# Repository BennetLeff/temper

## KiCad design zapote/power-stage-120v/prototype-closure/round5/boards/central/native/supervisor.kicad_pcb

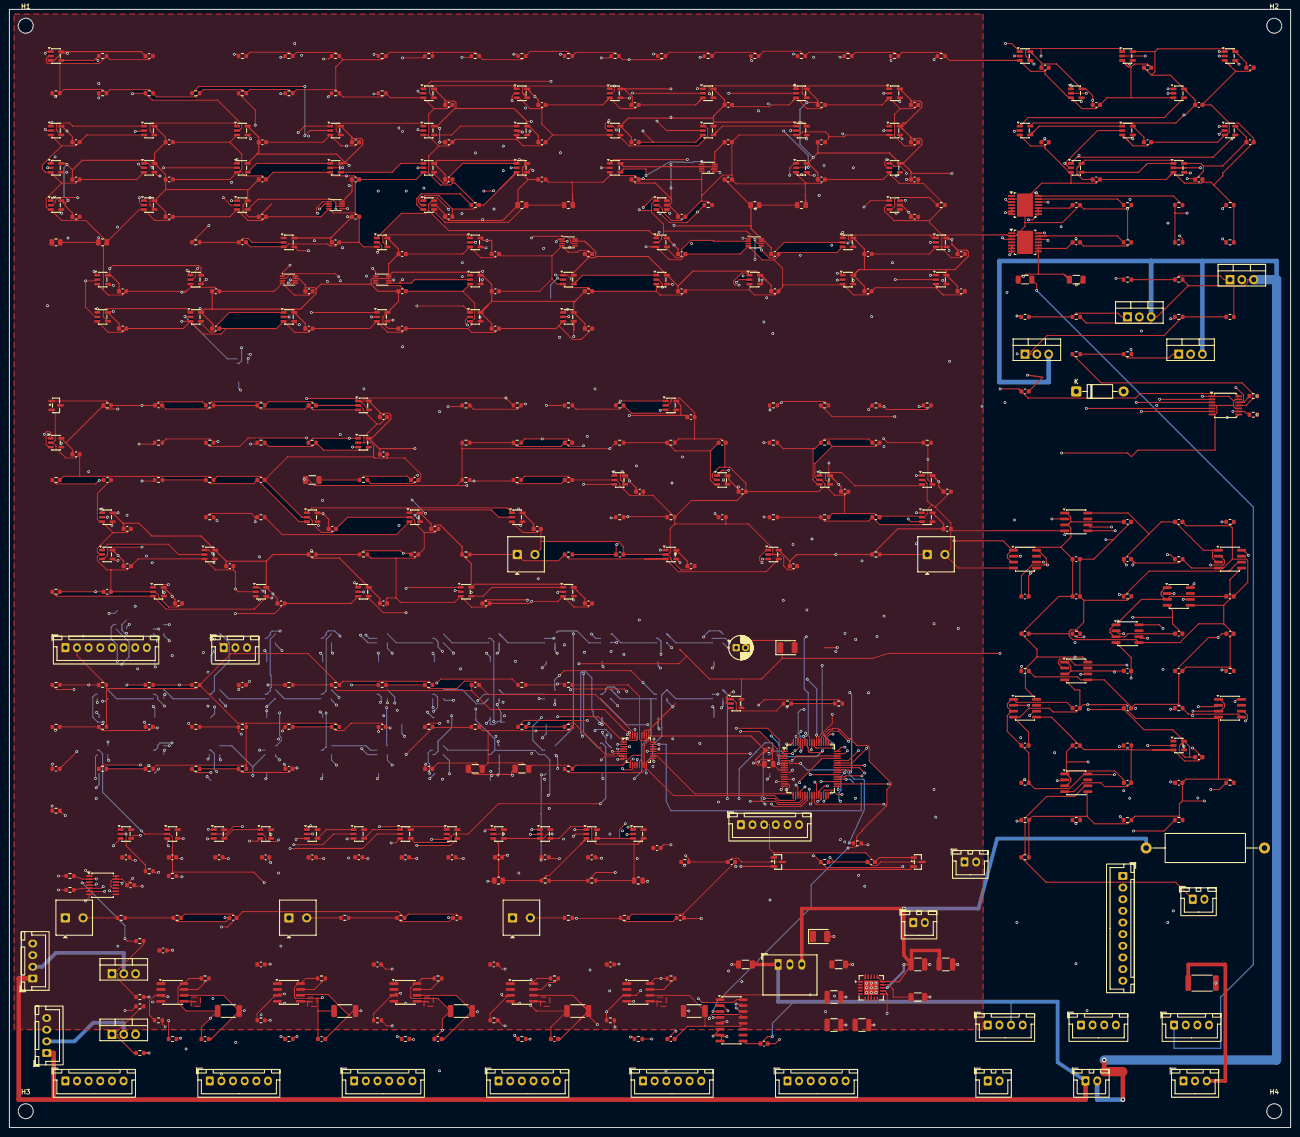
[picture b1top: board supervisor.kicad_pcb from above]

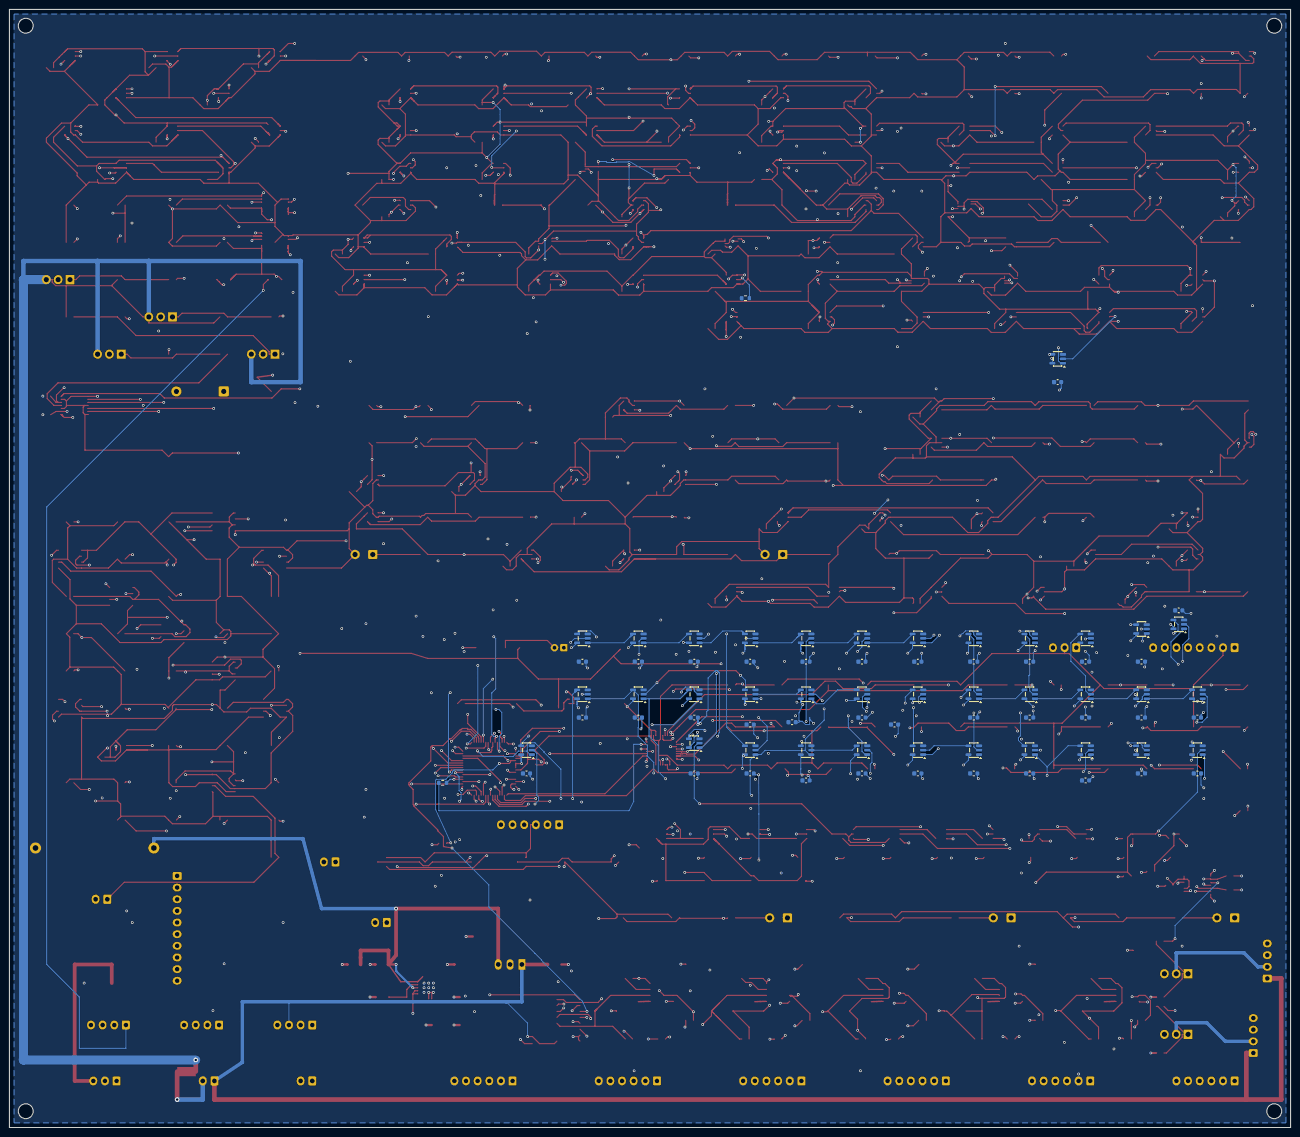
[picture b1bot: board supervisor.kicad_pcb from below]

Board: 4 copper layers, 275.0 x 240.0 mm, 600 parts (74 on the bottom side), 318 nets.

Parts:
C1: 22uF EEUFR1H220; CP_Radial_D5.0mm_P2.00mm
C2, C4: 22uF T491B226K016AT; CP_EIA-3528-21_Kemet-B
C3, C153: 1uF C1206C105K5RAC 50V; C_1206_3216Metric
C5, C17, C19, C20, C21, C22, C30, C31, C32, C33, C34, C35, C36, C37, C40, C41, C42, C45, C46, C48, C49, C50, C51, C52, C56, C57, C58, C59, C60, C61, C62, C63, C64, C65, C66, C67, C68, C69, C70, C71, C72, C73, C74, C75, C76, C77, C78, C79, C80, C81, C82, C83, C84, C85, C86, C87, C88, C90, C91, C92, C93, C94, C95, C96, C97, C98, C99, C100, C101, C102, C103, C104, C105, C106, C107, C108, C109, C110, C111, C112, C113, C114, C115, C116, C117, C118, C119, C120, C121, C122, C123, C124, C125, C126, C127, C128, C129, C130, C131, C132, C133, C134, C135, C136, C137, C138, C139, C140, C141, C142, C143, C144, C145, C146, C155, C157, C159, C161, C163, C165, C166, C167, C168, C169, C170, C171, C172, C173, C174, C175, C176, C177, C178, C179, C180, C181, C182, C183, C184, C185, C186, C187, C188, C189, C190, C191, C192, C193, C194, C195, C196, C197, C198, C199, C200, C201, C202, C203, C204, C205, C206, C207, C208, C209, C210, C211, C212, C213: 100nF C0603C104K5RACAUTO; C_0603_1608Metric
C6, C7, C8, C89: 10nF C0603C103K5RACAUTO; C_0603_1608Metric
C9, C10, C11, C12, C13, C14, C15, C16, C18, C23, C24, C25, C26, C27, C28, C29, C38, C39, C43, C44, C47: 1nF C0603C102J5GACTU; C_0603_1608Metric
C53: 220nF C0603C224K4RACAUTO; C_0603_1608Metric
C54, C55: 1uF 12063C105KAT2A; C_1206_3216Metric
C147: 4.7uF C2012X7R1E475K125AB; C_0805_2012Metric
C148, C149, C150, C151, C152: 22uF GRM32ER71E226KE15L 25V X7R; C_1210_3225Metric
C154, C156, C158, C160, C162: 1nF C0603C102J5GACTU 50V; C_0603_1608Metric
C164: 100nF C0603C104J5RACTU 50V; C_0603_1608Metric
D1, D2: BAV199,215; SOT-23
D3: 1N4007-E3/54; D_DO-41_SOD81_P10.16mm_Horizontal
H1, H2, H3, H4: MountingHole_3.2mm_M3
J1, J2, J3, J5, J6: 1725669 Phoenix MKDS1/2-3.81; TerminalBlock_Phoenix_MKDS-1-2-3.81_1x02_P3.81mm_Horizontal
J4, J11, J18, J19, J20, J21, J22: B6B-XH-A(LF)(SN); JST_XH_B6B-XH-A_1x06_P2.50mm_Vertical
J7, J13: B3B-XH-A(LF)(SN); JST_XH_B3B-XH-A_1x03_P2.50mm_Vertical
J8: B8B-XH-A(LF)(SN); JST_XH_B8B-XH-A_1x08_P2.50mm_Vertical
J9: B10B-XH-A(LF)(SN); JST_XH_B10B-XH-A_1x10_P2.50mm_Vertical
J10, J12, J17, J23, J24: B2B-XH-A(LF)(SN); JST_XH_B2B-XH-A_1x02_P2.50mm_Vertical
J14, J15, J16, J25, J26: B4B-XH-A(LF)(SN); JST_XH_B4B-XH-A_1x04_P2.50mm_Vertical
N1: PCB copper star 2mm; NetTie-2_SMD_Pad2.0mm
Q1, Q2, Q3, Q4, Q5, Q6: IRL540NPBF; TO-220-3_Vertical
R1: 82R 1% CRCW251282R0FKEG 1W; R_2512_6332Metric
R2, R5, R7, R9, R35, R36, R75, R77, R122, R124, R126, R128, R174, R176: 1kR CRCW06031K00FKEA; R_0603_1608Metric
R3, R6, R8, R10, R78, R79, R80, R81, R82, R83, R84, R85, R86, R87, R88, R89, R90, R91, R92, R93, R94, R95, R96, R97, R113, R115, R116, R118, R119, R136, R137, R138, R139, R140, R141, R142, R143, R144, R145, R146, R147, R148, R149, R150, R151, R168, R169, R178, R180, R181, R182, R183: 10kR CRCW060310K0FKEA; R_0603_1608Metric
R4, R66, R67: 20kR CRCW060320K0FKEA; R_0603_1608Metric
R11, R12, R13, R14, R15, R16, R17, R18, R19, R20, R21, R22, R23, R24, R25, R26, R27, R28, R29, R30, R31, R32, R33, R34, R38, R39, R41, R43, R45, R47, R49, R51, R69, R72, R74, R76, R171, R172: 10kR 0.1% TNPW060310K0BEEA; R_0603_1608Metric
R37: 330R CRCW0603330RFKEA; R_0603_1608Metric
R40, R42, R44, R46, R48, R50: 20kR 0.1% TNPW060320K0BEEA; R_0603_1608Metric
R52: 62.6kR 0.1% TNPW060362K6BEEA; R_0603_1608Metric
R53, R55, R57, R59, R61, R63, R65, R71, R73: 100kR 0.1% TNPW0603100KBEEA; R_0603_1608Metric
R54: 60.1kR 0.1% TNPW060360K1BEEA; R_0603_1608Metric
R56: 57.8kR 0.1% TNPW060357K8BEEA; R_0603_1608Metric
R58: 173kR 0.1% TNPW0603173KBEEA; R_0603_1608Metric
R60: 6.34kR 0.1% TNPW06036K34BEEA; R_0603_1608Metric
R62: 1.56MR 0.1% TNPW12061M56BEEA; R_1206_3216Metric
R64: 284kR 0.1% TNPW0603284KBEEA; R_0603_1608Metric
R68: 110kR 0.1% TNPW0603110KBEEA; R_0603_1608Metric
R70: 49.9kR 0.1% TNPW060349K9BEEA; R_0603_1608Metric
R98, R99, R100, R101, R102, R103: 47kR CRCW060347K0FKEA; R_0603_1608Metric
R104: 54.2kR 0.1% TNPW060354K2BEEA; R_0603_1608Metric
R105, R108, R111: 1MR 0.1% TNPW08051M00BEEA; R_0805_2012Metric
R106, R109: 681kR 0.1% TNPW0805681KBEEA; R_0805_2012Metric
R107: 81.1kR 0.1% TNPW060381K1BEEA; R_0603_1608Metric
R110: 191kR 0.1% TNPW0603191KBEEA; R_0603_1608Metric
R112: 523kR 0.1% TNPW0805523KBEEA; R_0805_2012Metric
R114, R117: 4.87kR 0.1% TNPW06034K87BEEA; R_0603_1608Metric
R120, R121: 0R CRCW12060000Z0EA; R_1206_3216Metric
R123, R125, R127, R129, R175, R177: 22kR CRCW060322K0FKEA; R_0603_1608Metric
R130, R132, R134, R155, R157, R159, R160, R163, R164, R167: 100kR CRCW0603100KFKEA; R_0603_1608Metric
R131, R133, R135, R161, R165: 562R CRCW0603562RFKEA; R_0603_1608Metric
R152: 33R CRCW060333R0FKEA; R_0603_1608Metric
R153: 300R 0.1% TNPW1206300RBEEA; R_1206_3216Metric
R154, R156, R158, R162, R166: 4.7kR CRCW20104K70FKEF 0.75W; R_2010_5025Metric
R170, R173: 620kR 0.1% TNPW0805620KBEEA; R_0805_2012Metric
R179: 39R 1% PR03000203909FAC00 3W; R_Axial_DIN0617_L17.0mm_D6.0mm_P25.40mm_Horizontal
U1: R-78B5.0-1.0; Converter_DCDC_RECOM_R-78HB-0.5_THT
U2: TPS3820-33DBVR; SOT-23-5
U3: TPS3825-50DBVR; SOT-23-5
U4: LM4040A25IDBZR; SOT-23
U5, U6, U7, U8: TLV9061IDBVR; SOT-23-5
U9, U10, U11, U12, U14, U15, U17, U18, U20, U21, U22, U23, U124, U125, U127, U128: TLV3201AIDBVR; SOT-23-5
U13, U16, U19, U24, U25, U26, U28, U29, U30, U31, U32, U33, U34, U35, U36, U37, U38, U39, U40, U41, U42, U46, U47, U48, U49, U50, U52, U53, U54, U56, U65, U67, U68, U69, U70, U72, U73, U74, U75, U76, U77, U78, U79, U80, U81, U84, U85, U86, U88, U89, U90, U91, U92, U93, U94, U118, U119, U120, U121, U122, U123, U126, U129, U133, U134, U135, U136, U137, U138, U139, U140, U141, U142, U143, U144, U146, U147, U149, U150, U151, U152, U155, U156, U158, U159, U161, U162, U163, U164: SN74LVC1G08DBVR; SOT-23-5
U27: ADS131M08IPBSR; TQFP-32_5x5mm_P0.5mm
U43, U55, U83, U106, U116, U117, U130, U131, U132, U145, U154, U157: SN74LVC1G04DBVR; SOT-23-5
U44, U45, U62, U63, U87, U148, U160: SN74LVC1G32DBVR; SOT-23-5
U51, U57, U64, U66, U71, U82: SN74LVC1G74DCUR; VSSOP-8_2.3x2mm_P0.5mm
U58, U59, U60: LTC6993HS6-1#TRMPBF; TSOT-23-6
U61: SN74LVC1G17DBVR; SOT-23-5
U95, U96: TPS1H100AQPWPRQ1; Texas_HTSSOP-14-1EP_4.4x5mm_P0.65mm_EP3.4x5mm_Mask3.155x3.2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
U97, U153: SN74AHCT125PWR; TSSOP-14_4.4x5mm_P0.65mm
U98, U99, U100, U101, U103, U104, U105, U107: ISO7710FDR; SOIC-8_3.9x4.9mm_P1.27mm
U102: ISO7710DR; SOIC-8_3.9x4.9mm_P1.27mm
U108: STM32G071RBT6; LQFP-64_10x10mm_P0.5mm
U109: TPS7A4700RGWR; Texas_RGW0020A_VQFN-20-1EP_5x5mm_P0.65mm_EP3.15x3.15mm
U110, U111, U112, U113, U114: ISO1211DR; SOIC-8_3.9x4.9mm_P1.27mm
U115: TPL7407LDR; SOIC-16_3.9x9.9mm_P1.27mm

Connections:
ADC_CAP: C53.1, U27.24
ADC_CLKIN: J7.3, R152.2, U27.23
ADC_CS_N: R79.1, U27.17, U108.21
ADC_DIN: U27.21, U108.24
ADC_DOUT: U27.20, U108.23
ADC_DRDY_N: U27.18, U108.17
ADC_MCO_SOURCE: R152.1, U108.36
ADC_RESET_N: R78.1, U27.16, U108.18
ADC_SCLK: U27.19, U108.22
ADMIT: R178.1, U57.1, U108.5, U154.2
ADMIT_LOW: U154.4, U156.2
ADMIT_VALID: U159.4, U160.2
ALL_BUDGET_OK: U46.4, U47.1
ATTEMPT: R113.1, U57.5, U58.1, U59.1, U65.2, U66.6, U68.2, U78.2, U80.2, U108.58, U146.1, U157.2, U160.1, U161.1, U163.1
ATTEMPT_CLEAR_N: U56.4, U57.6, U158.1
ATTEMPT_D: U57.2, U160.4
ATTEMPT_RC: C89.1, R113.2, U61.2
AUX_0V: C1.2, C2.2, C3.2, C4.2, C5.2, C6.2, C7.2, C8.2, C15.2, C16.2, C17.2, C18.2, C19.2, C20.2, C21.2, C22.2, C23.2, C24.2, C25.2, C26.2, C27.2, C28.2, C29.2, C30.2, C31.2, C32.2, C33.2, C34.2, C35.2, C36.2, C37.2, C38.2, C39.2, C40.2, C41.2, C42.2, C43.2, C44.2, C45.2, C46.2, C47.2, C48.2, C49.2, C50.2, C51.2, C52.2, C53.2, C54.2, C55.2, C56.2, C57.2, C58.2, C59.2, C60.2, C61.2, C62.2, C63.2, C64.2, C65.2, C66.2, C67.2, C68.2, C69.2, C70.2, C71.2, C72.2, C73.2, C74.2, C75.2, C76.2, C77.2, C78.2, C79.2, C80.2, C81.2, C82.2, C83.2, C84.2, C85.2, C86.2, C87.2, C88.2, C89.2, C90.2, C91.2, C92.2, C93.2, C94.2, C95.2, C96.2, C97.2, C98.2, C99.2, C100.2, C101.2, C102.2, C103.2, C104.2, C105.2, C106.2, C107.2, C108.2, C109.2, C110.2, C111.2, C112.2, C113.2, C114.2, C115.2, C116.2, C117.2, C118.2, C119.2, C120.2, C121.2, C122.2, C123.2, C124.2, C125.2, C126.2, C127.2, C129.2, C132.2, C134.2, C136.2, C138.2, C140.2, C142.2, C143.2, C144.2, C146.2, C147.2, C148.2, C149.2, C150.2, C151.2, C152.2, C153.2, C155.2, C157.2, C159.2, C161.2, C163.2, C164.2, C165.2, C166.2, C167.2, C168.2, C169.2, C170.2, C171.2, C172.2, C173.2, C174.2, C175.2, C176.2, C177.2, C178.2, C179.2, C180.2, C181.2, C182.2, C183.2, C184.2, C185.2, C186.2, C187.2, C188.2, C189.2, C190.2, C191.2, C192.2, C193.2, C194.2, C195.2, C196.2, C197.2, C198.2, C199.2, C200.2, C201.2, C202.2, C203.2, C204.2, C205.2, C206.2, C207.2, C208.2, C209.2, C210.2, C211.2, C212.2, C213.2, D1.1, D2.1, J4.2, J4.6, J5.2, J6.2, J7.2, J8.2, J11.3, J12.2, J13.2, J18.2, J18.6, J19.2, J19.6, J20.2, J20.6, J21.2, J21.6, J22.2, J22.6, N1.2, R1.2, R2.2, R4.2, R6.2, R8.2, R10.2, R12.2, R14.2, R16.2, R18.2, R20.2, R22.2, R24.2, R26.2, R28.2, R30.2, R32.2, R34.2, R39.2, R53.2, R55.2, R57.2, R59.2, R61.2, R63.2, R65.2, R69.2, R71.2, R73.2, R78.2, R80.2, R81.2, R82.2, R83.2, R84.2, R85.2, R86.2, R87.2, R88.2, R89.2, R90.2, R91.2, R92.2, R93.2, R94.2, R95.2, R96.2, R97.2, R98.2, R99.2, R100.2, R101.2, R102.2, R103.2, R104.2, R106.2, R107.2, R109.2, R110.2, R112.2, R114.2, R116.2, R117.2, R119.2, R130.2, R132.2, R134.2, R138.2, R139.2, R140.2, R141.2, R142.2, R143.2, R151.2, R153.2, R155.2, R157.2, R159.2, R160.2, R163.2, R164.2, R167.2, R168.2, R169.2, R173.2, R178.2, R179.2, R180.2, R181.2, R182.2, R183.2, U1.2, U2.2, U3.2, U4.2, U5.2, U6.2, U7.2, U8.2, U9.2, U10.2, U11.2, U12.2, U13.3, U14.2, U15.2, U16.3, U17.2, U18.2, U19.3, U20.2, U21.2, U22.2, U23.2, U24.3, U25.3, U26.3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
AUX_24V: C1.1, C3.1, C124.1, C125.1, C164.1, J12.1, J13.1, J14.3, J15.3, J16.3, J25.1, J25.3, J26.1, J26.3, R68.1, R120.1, R121.1, U1.1, U95.8, U95.9, U95.10, U96.8, U96.9, U96.10, U115.9
BASIC_HEALTHY: U42.4, U46.1, U108.63, U149.1
BUDGET_OR_PROOF: U44.4, U45.2, U161.2
BUS_DISCHARGED: U126.4, U133.1
BUS_LIMIT_OK: J8.3, R80.1, U9.1, U31.2
BUS_SAFE_HI: U124.1, U126.1
BUS_SAFE_LO: U125.1, U126.2
BUS_TRIP: C23.1, R52.2, R53.1, U9.3
BYPASS_PROVEN: U71.5, U88.2, U108.59
CAPS_BUS_DIAG_OK: U134.4, U135.1
CAPS_DISCHARGED: U135.4, U136.1
CAPS_WINDOWS_OK: U133.4, U134.1
CATCH_DISCHARGED: U129.4, U133.2
CATCH_LIMIT_OK: J8.4, R81.1, U10.1, U32.2
CATCH_SAFE_HI: U127.1, U129.1
CATCH_SAFE_LO: U128.1, U129.2
CATCH_TRIP: C24.1, R54.2, R55.1, U10.3
CMD_K1: R93.1, U73.2, U97.2, U108.25, U130.2
CMD_K2: R94.1, U75.2, U97.5, U108.26, U131.2
CMD_KB: R95.1, U76.1, U108.27, U132.2
CMD_KPA: R168.1, U108.40, U116.2, U151.2
CMD_KPB: R169.1, U108.41, U117.2, U152.2
CMD_KT: R96.1, U67.1, U79.1, U108.28
COIL_RET: N1.1, Q1.3, Q2.3, Q3.3, Q4.3, Q5.3, Q6.3, R123.2, R125.2, R127.2, R129.2, R175.2, R177.2
CTRL_3V3: C128.1, C130.1, C131.1, C133.1, C135.1, C137.1, C139.1, C141.1, C145.1, J9.1, R144.2, U98.8, U99.8, U100.1, U100.3, U101.1, U101.3, U102.1, U102.3, U103.1, U103.3, U104.1, U104.3, U105.1, U105.3, U107.8
CTRL_FAULT_HIGH: J9.6, R144.1, U102.2
CTRL_FAULT_LOCAL: R140.1, U102.6, U106.2, U108.2
CTRL_GND: C128.2, C130.2, C131.2, C133.2, C135.2, C137.2, C139.2, C141.2, C145.2, J9.2, J10.2, R136.2, R137.2, R145.2, R146.2, R147.2, R148.2, R149.2, R150.2, U98.5, U99.5, U100.4, U101.4, U102.4, U103.4, U104.4, U105.4, U107.5
CTRL_HEARTBEAT: J9.5, R146.1, U101.2
CTRL_HEARTBEAT_LOCAL: R139.1, U101.6, U108.53
CTRL_HEARTBEAT_OK: R151.1, U84.2, U91.2, U108.54
CTRL_INTERLOCK_OK: J9.10, R148.1, U105.2
CTRL_INTERLOCK_OK_LOCAL: R143.1, U86.2, U94.2, U105.6, U108.43
CTRL_PWM_REQUEST: J9.4, R145.1, U100.2
CTRL_PWM_REQUEST_LOCAL: R138.1, U93.2, U100.6, U108.64
CTRL_RAIL_OK: J9.9, R147.1, U104.2
CTRL_RAIL_OK_LOCAL: R142.1, U84.1, U104.6, U108.1
CTRL_RX: J9.8, R137.1, U99.6
CTRL_TX: J9.7, R149.1, U103.2
FAULT_CHAIN_HEALTHY: U48.4, U49.1
FAULT_CLEAR_N: U49.4, U51.6
FAULT_PRE_RUNTIME: U47.4, U48.1
FINAL_PROOF_CLEAR_N: U71.6, U82.6, U163.4
FINAL_PROOF_VALID: U71.2, U162.4
ILINE_ADC: C16.1, D2.3, R36.2, U27.12
ILINE_GUARD_HI: R66.2, U14.4
ILINE_GUARD_LO: R67.2, U15.3
ILINE_HI: C27.1, R60.2, R61.1, U14.3
ILINE_HI_OK: U14.1, U16.1
ILINE_LIMIT_OK: J8.6, R83.1, U16.4, U34.2
ILINE_LO: C28.1, R62.2, R63.1, U15.4
ILINE_LO_OK: U15.1, U16.2
ILINE_RAW: J24.1, R36.1, R66.1, R67.1
IPROOF_ADC: C15.1, D1.3, R35.2, U27.9
IPROOF_RAW: J23.1, R35.1
ISO_ALLOW_OR: U148.4, U150.2
ISO_COIL_ALLOWED: U150.4, U151.1, U152.1
ISO_HEALTH: U149.4, U150.1, U155.2
ISO_RUN_1: U118.4, U119.1
ISO_RUN_2: U119.4, U120.1
ISO_RUN_3: U120.4, U121.1
ISO_RUN_4: U121.4, U122.1
ISO_TIMED_ATTEMPT: U146.4, U147.1
ISO_TIMED_NO_RUN: U147.4, U148.2
K1_BUF: R122.1, U97.3
K1_CL: R114.1, U95.13
K1_CMD_OFF: U130.4, U142.2
K1_COIL_HIGH: J14.1, U95.5, U95.6, U95.7
K1_COIL_LOW: J14.2, Q1.2
K1_FB_EXC: R155.1, U108.50, U115.1, U139.2
K1_FB_IN: R131.2, U110.7
K1_FB_SINK: C154.2, R154.2, U110.6, U115.16
K1_GATE: Q1.1, R122.2, R123.1
K1_HIGH_EN: R116.1, U73.4, U95.3
K1_MIRROR: R130.1, U108.39, U110.3, U136.2
K1_MIRROR_24V: C154.1, J14.4, R131.1, R154.1, U110.8
K1_ST_N: R115.2, U95.14, U108.55
K2_BUF: R124.1, U97.6
K2_CL: R117.1, U96.13
K2_CMD_OFF: U131.4, U143.2
K2_COIL_HIGH: J15.1, U96.5, U96.6, U96.7
K2_COIL_LOW: J15.2, Q2.2
K2_FB_EXC: R157.1, U108.51, U115.2, U140.2
K2_FB_IN: R133.2, U111.7
K2_FB_SINK: C156.2, R156.2, U111.6, U115.15
K2_GATE: Q2.1, R124.2, R125.1
K2_HIGH_EN: R119.1, U75.4, U96.3
K2_MIRROR: R132.1, U108.48, U111.3, U137.2
K2_MIRROR_24V: C156.1, J15.4, R133.1, R156.1, U111.8
K2_ST_N: R118.2, U96.14, U108.56
KB_BUF: R126.1, U97.8
KB_CMD_OFF: U132.4, U144.2
KB_COIL_HIGH: J16.1, R120.2
KB_COIL_LOW: J16.2, Q3.2
KB_DRIVE: R180.1, U78.4, U97.9
KB_FB_EXC: R159.1, U108.52, U115.3, U141.2
KB_FB_IN: R135.2, U112.7
KB_FB_SINK: C158.2, R158.2, U112.6, U115.14
KB_GATE: Q3.1, R126.2, R127.1
KB_MIRROR: R134.1, U108.49, U112.3, U138.2
KB_MIRROR_24V: C158.1, J16.4, R135.1, R158.1, U112.8
KPA_BUF: R174.1, U153.3
KPA_CMD_OFF: U116.4, U121.2
KPA_COIL_LOW: J25.2, Q5.2
KPA_DRIVE: R182.1, U151.4, U153.2
KPA_FB_EXC: R163.1, U108.44, U115.4, U119.2
KPA_FB_IN: R161.2, U113.7
KPA_FB_SINK: C160.2, R162.2, U113.6, U115.13
KPA_GATE: Q5.1, R174.2, R175.1
KPA_MIRROR: R160.1, U108.3, U113.3, U118.1
KPA_MIRROR_24V: C160.1, J25.4, R161.1, R162.1, U113.8
KPB_BUF: R176.1, U153.6
KPB_CMD_OFF: U117.4, U122.2
KPB_COIL_LOW: J26.2, Q6.2
KPB_DRIVE: R183.1, U152.4, U153.5
KPB_FB_EXC: R167.1, U108.47, U115.5, U120.2
KPB_FB_IN: R165.2, U114.7
KPB_FB_SINK: C162.2, R166.2, U114.6, U115.12
KPB_GATE: Q6.1, R176.2, R177.1
KPB_MIRROR: R164.1, U108.4, U114.3, U118.2
KPB_MIRROR_24V: C162.1, J26.4, R165.1, R166.1, U114.8
KT_BUF: R128.1, U97.11
KT_COIL_LOW: D3.2, J17.2, Q4.2
KT_DRIVE: R181.1, U81.4, U97.12
KT_GATE: Q4.1, R128.2, R129.1
LATCH_OK: U51.5, U54.2, U56.1, U69.2, U72.2, U74.2, U77.2, U81.2, U89.2, U108.57, U149.2
MCU_BYPASS_PROVEN: R90.1, U71.1, U108.33
MCU_HEALTHY: R86.1, U42.2, U108.29
MCU_POST_OK: R87.1, U53.2, U108.30
MCU_PRECHARGE_DONE: R89.1, U66.1, U108.32
MCU_RESET_OK: R88.1, U50.2, U108.31
MCU_RUN: R91.1, U88.1, U108.34
MCU_STOP_DONE: R92.1, U55.2, U108.35
MCU_UART_RX: R141.1, U103.6, U108.42
MCU_UART_TX: U99.2, U108.37
MCU_WDI: R2.1, U2.4, U108.16
NATIVE_FAULT_N: U85.2, U92.2, U106.4
NATIVE_PERMIT: J10.1, R150.1, U107.6
NOT_ATTEMPT: U157.4, U158.2
NOT_RUN_PERMIT: U145.4, U147.2
PERMIT_LOCAL: U94.4, U107.2
PG5_N: R3.2, R4.1, U29.2
PG5_RAW: R3.1, U3.1
POD_3V3: C4.1, C5.1, C19.1, C20.1, C21.1, C22.1, C30.1, C31.1, C32.1, C33.1, C34.1, C35.1, C36.1, C37.1, C40.1, C41.1, C42.1, C45.1, C46.1, C48.1, C49.1, C50.1, C51.1, C52.1, C54.1, C55.1, C56.1, C57.1, C58.1, C59.1, C60.1, C61.1, C62.1, C63.1, C64.1, C65.1, C66.1, C67.1, C68.1, C69.1, C70.1, C71.1, C72.1, C73.1, C74.1, C75.1, C76.1, C77.1, C78.1, C79.1, C80.1, C81.1, C82.1, C83.1, C84.1, C85.1, C86.1, C87.1, C88.1, C90.1, C91.1, C92.1, C93.1, C94.1, C95.1, C96.1, C97.1, C98.1, C99.1, C100.1, C101.1, C102.1, C103.1, C104.1, C105.1, C106.1, C107.1, C108.1, C109.1, C110.1, C111.1, C112.1, C113.1, C114.1, C115.1, C116.1, C117.1, C118.1, C119.1, C120.1, C121.1, C122.1, C123.1, C127.1, C129.1, C132.1, C134.1, C136.1, C138.1, C140.1, C142.1, C143.1, C144.1, C146.1, C147.1, C150.1, C151.1, C152.1, C155.1, C157.1, C159.1, C161.1, C163.1, C165.1, C166.1, C167.1, C168.1, C169.1, C170.1, C171.1, C172.1, C173.1, C174.1, C175.1, C176.1, C177.1, C178.1, C179.1, C180.1, C181.1, C182.1, C183.1, C184.1, C185.1, C186.1, C187.1, C188.1, C189.1, C190.1, C191.1, C192.1, C193.1, C194.1, C195.1, C196.1, C197.1, C198.1, C199.1, C200.1, C201.1, C203.1, C204.1, C205.1, C206.1, C207.1, C208.1, C209.1, C210.1, C211.1, C212.1, C213.1, D1.2, D2.2, J1.1, J2.1, J3.1, J4.1, J7.1, J8.1, J11.1, J18.1, J19.1, J20.1, J21.1, J22.1, R37.1, R72.1, R74.1, R76.1, R79.2, R105.1, R108.1, R111.1, R115.1, R118.1, R153.1, U2.3, U2.5, U5.5, U6.5, U7.5, U8.5, U9.5, U10.5, U11.5, U12.5, U13.5, U14.5, U15.5, U16.5, U17.5, U18.5, U19.5, U20.5, U21.5, U22.5, U23.5, U24.5, U25.5, U26.5, U27.15, U27.26, U28.5, U29.5, U30.5, U31.5, U32.5, U33.5, U34.5, U35.5, U36.5, U37.5, U38.5, U39.5, U40.5, U41.5, U42.5, U43.5, U44.5, U45.5, U46.5, U47.5, U48.5, U49.5, U50.5, U51.2, U51.7, U51.8, U52.5, U53.5, U54.5, U55.5, U56.5, U57.7, U57.8, U58.5, U59.5, U60.5, U61.5, U62.5, U63.5, U64.7, U64.8, U65.5, U66.7, U66.8, U67.5, U68.5, U69.5, U70.5, U71.7, U71.8, U72.5, U73.5, U74.5, U75.5, U76.5, U77.5, U78.5, U79.5, U80.5, U81.5, U82.2, U82.7, U82.8, U83.5, U84.5, U85.5, U86.5, U87.5, U88.5, U89.5, U90.5, U91.5, U92.5, U93.5, U94.5, U95.12, U96.12, U98.1, U98.3, U99.1, U99.3, U100.8, U101.8, U102.8, U103.8, U104.8, U105.8, U106.5, U107.1, U107.3, U108.6, U108.7, U108.8, U109.1, U109.3, U109.20, U110.1, U110.2, U111.1, U111.2, U112.1, U112.2, U113.1, U113.2, U114.1, U114.2, U116.5, U117.5, U118.5, U119.5, U120.5, U121.5, U122.5, U123.5, U124.5, U125.5, U126.5, U127.5, U128.5, U129.5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
POD_5V: C2.1, C126.1, C202.1, J13.3, R1.1, U3.4, U3.5, U97.14, U153.10, U153.13, U153.14
POD_24V_ACT: D3.1, J17.1, R121.2
POD_RESET: C7.1, R7.2, R8.1, U50.1, U108.14
POD_RESET_RAW: J2.2, R7.1
POD_START: C6.1, R5.2, R6.1, U52.1, U108.13
POD_START_RAW: J1.2, R5.1
POD_STOP: C8.1, R9.2, R10.1, U28.1, U108.15
POD_STOP_RAW: J3.2, R9.1
PRECHARGE_DONE: U62.2, U66.5, U67.2, U70.2, U76.2
PRECHARGE_ISOLATED: U122.4, U123.2, U162.2, U163.2
PRE_CAPTURE_VALID: U65.4, U66.2
PRE_ISO_RUN_OK: U92.4, U123.1
PROOF_CAPTURE_VALID: U70.4, U162.1
PROOF_REQUEST: U60.1, U69.4
PROOF_WINDOW: U60.6, U70.1, U79.2, U108.62
RAIL24_DIV: C38.1, R68.2, R69.1, U17.3, U18.4
RAIL24_HI_OK: U18.1, U19.2
RAIL24_LO: C39.1, R70.2, R71.1, U17.4
RAIL24_LO_OK: U17.1, U19.1
RAIL24_OK: J8.8, R85.1, U19.4, U30.2
REF_1V25: J23.2, J24.2, R41.1, R45.1, R49.1, R171.2, R172.1, U5.1, U5.4, U27.10, U27.11
REF_2V5: C17.1, R37.2, R38.1, R52.1, R54.1, R56.1, R58.1, R60.1, R62.1, R64.1, R70.1, R170.1, U4.1, U18.3
REF_HALF: C18.1, R38.2, R39.1, U5.3
REG3_5V: C148.1, C149.1, R179.1, U1.3, U109.13, U109.15, U109.16
REG3_NR: C153.1, U109.14
RESET_QUALIFIED: U50.4, U51.1
RP1_TEMP: J5.1, R74.2, R75.1, U20.3, U21.4
RP1_TEMP_ADC: C44.1, R75.2, U108.19
RP2_TEMP: J6.1, R76.2, R77.1, U22.3, U23.4
RP2_TEMP_ADC: C47.1, R77.2, U108.20
RP_TEMP_OK: J8.7, R84.1, U26.4, U35.2
RUNTIME_ALLOWED: U48.2, U87.4
RUNTIME_HEALTHY: U86.4, U87.2, U90.2, U164.2
RUN_ARMED: U82.5, U83.2, U164.1
RUN_NOT_ARMED: U83.4, U87.1
SAFE_HI: R170.2, R171.1, U124.3, U127.3
SAFE_LO: R172.2, R173.1, U125.4, U128.4
SESSION_BUDGET_OK: U44.2, U164.4
SOURCE_DRIVE_TIMED: U72.1, U74.1, U161.4
SOURCE_OFF_1: U136.4, U137.1
SOURCE_OFF_2: U137.4, U138.1
SOURCE_OFF_3: U138.4, U139.1
SOURCE_OFF_4: U139.4, U140.1
SOURCE_OFF_5: U140.4, U141.1
SOURCE_OFF_6: U141.4, U142.1
SOURCE_OFF_7: U142.4, U143.1
SOURCE_OFF_8: U143.4, U144.1
SOURCE_OFF_PHYSICAL: U144.4, U148.1, U155.1
START_BUDGET_OK: U47.2, U63.4
START_OR_DONE: U62.4, U63.1
START_QUALIFIED: U54.4, U64.1
START_RELEASED: R97.1, U52.2, U108.38
START_TOKEN: U64.5, U159.1
START_WINDOW: U58.6, U62.1, U65.1, U108.61
STOP_DONE_N: U49.2, U55.4, U56.2
SUP_RUN_OK: J9.3, R136.1, U98.6
SUP_RUN_OK_LOCAL: U82.1, U93.1, U98.2, U123.4, U145.2
SWCLK: J11.4, U108.46
SWDIO: J11.2, U108.45
TANK_HI: C25.1, R56.2, R57.1, U11.3
TANK_HI_OK: U11.1, U13.1
TANK_LIMIT_OK: J8.5, R82.1, U13.4, U33.2
TANK_LO: C26.1, R58.2, R59.1, U12.4
TANK_LO_OK: U12.1, U13.2
TEMP1_HI_OK: U21.1, U24.2
TEMP1_LO_OK: U20.1, U24.1
TEMP2_HI_OK: U23.1, U26.2
TEMP2_LO_OK: U22.1, U25.2
TEMP_HI: C43.1, R72.2, R73.1, U21.3, U23.3
TEMP_LO: C29.1, R64.2, R65.1, U20.4, U22.4
TIMER_ARMED: U43.2, U61.4
TIMER_NOT_ARMED: U43.4, U45.1, U63.2
TOKEN_ARM_VALID: U64.2, U156.4
TOKEN_CLEAR_N: U64.6, U158.4
TOKEN_SAFE: U155.4, U156.1, U159.2
TOTAL_BUDGET_OK: U45.4, U46.2
TOTAL_WINDOW: U44.1, U59.6, U108.60, U146.2
UT_PROOF_DIV: R111.2, R112.1, U60.4
UT_PROOF_SET: R110.1, U60.3
UT_START_DIV: R105.2, R106.1, U58.4
UT_START_SET: R104.1, U58.3
UT_TOTAL_DIV: R108.2, R109.1, U59.4
UT_TOTAL_SET: R107.1, U59.3
U_HEALTH_1: U28.4, U29.1
U_HEALTH_2: U29.4, U30.1
U_HEALTH_3: U30.4, U31.1
U_HEALTH_4: U31.4, U32.1
U_HEALTH_5: U32.4, U33.1
U_HEALTH_6: U33.4, U34.1
U_HEALTH_7: U34.4, U35.1
U_HEALTH_8: U35.4, U36.1
U_HEALTH_9: U36.4, U37.1
U_HEALTH_10: U37.4, U38.1
U_HEALTH_11: U38.4, U39.1
U_HEALTH_12: U39.4, U40.1
U_HEALTH_13: U40.4, U41.1
U_HEALTH_14: U41.4, U42.1
U_K1HI_1: U72.4, U73.1
U_K2HI_1: U74.4, U75.1
U_KBGATE_1: U76.4, U77.1
U_KBGATE_2: U77.4, U78.1
U_KTGATE_1: U79.4, U80.1
U_KTGATE_2: U80.4, U81.1
U_PERMIT_1: U93.4, U94.1
U_PROOFREQ_1: U67.4, U68.1
U_PROOFREQ_2: U68.4, U69.1
U_RUNTIME_1: U84.4, U85.1
U_RUNTIME_2: U85.4, U86.1
U_RUN_1: U88.4, U89.1
U_RUN_2: U89.4, U90.1
U_RUN_3: U90.4, U91.1
U_RUN_4: U91.4, U92.1
U_START_1: U52.4, U53.1
U_START_2: U53.4, U54.1
U_TEMPS_1: U24.4, U25.1
U_TEMPS_2: U25.4, U26.1
VBUS_ADC_N: C12.2, R25.2, R26.1, U27.3
VBUS_ADC_P: C12.1, R23.2, R24.1, U27.4
VBUS_DIAG_N: J21.5, R101.1, U39.2, U134.2
VBUS_DIFF_MINUS: R42.2, R43.2, U6.4
VBUS_DIFF_PLUS: R40.2, R41.2, U6.3
VBUS_GUARD: R43.1, U6.1, U9.4, U124.4, U125.3
VBUS_N: J21.4, R25.1, R42.1
VBUS_P: J21.3, R23.1, R40.1
VCATCH_ADC_N: C13.2, R29.2, R30.1, U27.6
VCATCH_ADC_P: C13.1, R27.2, R28.1, U27.5
VCATCH_DIAG_N: J4.5, R102.1, U40.2, U135.2
VCATCH_DIFF_MINUS: R46.2, R47.2, U7.4
VCATCH_DIFF_PLUS: R44.2, R45.2, U7.3
VCATCH_GUARD: R47.1, U7.1, U10.4, U127.4, U128.3
VCATCH_N: J4.4, R29.1, R46.1
VCATCH_P: J4.3, R27.1, R44.1
VLINE_ADC_N: C9.2, R13.2, R14.1, U27.30
VLINE_ADC_P: C9.1, R11.2, R12.1, U27.29
VLINE_DIAG_N: J18.5, R98.1, U36.2
VLINE_N: J18.4, R13.1
VLINE_P: J18.3, R11.1
VOUT_ADC_N: C11.2, R21.2, R22.1, U27.2
VOUT_ADC_P: C11.1, R19.2, R20.1, U27.1
VOUT_DIAG_N: J20.5, R100.1, U38.2
VOUT_N: J20.4, R21.1
VOUT_P: J20.3, R19.1
VPRE_ADC_N: C10.2, R17.2, R18.1, U27.31
VPRE_ADC_P: C10.1, R15.2, R16.1, U27.32
VPRE_DIAG_N: J19.5, R99.1, U37.2
VPRE_N: J19.4, R17.1
VPRE_P: J19.3, R15.1
VTANK_ADC_N: C14.2, R33.2, R34.1, U27.7
VTANK_ADC_P: C14.1, R31.2, R32.1, U27.8
VTANK_DIAG_N: J22.5, R103.1, U41.2
VTANK_DIFF_MINUS: R50.2, R51.2, U8.4
VTANK_DIFF_PLUS: R48.2, R49.2, U8.3
VTANK_GUARD: R51.1, U8.1, U11.4, U12.3
VTANK_N: J22.4, R33.1, R50.1
VTANK_P: J22.3, R31.1, R48.1
WD_RESET_N: J11.5, U2.1, U28.2, U108.10

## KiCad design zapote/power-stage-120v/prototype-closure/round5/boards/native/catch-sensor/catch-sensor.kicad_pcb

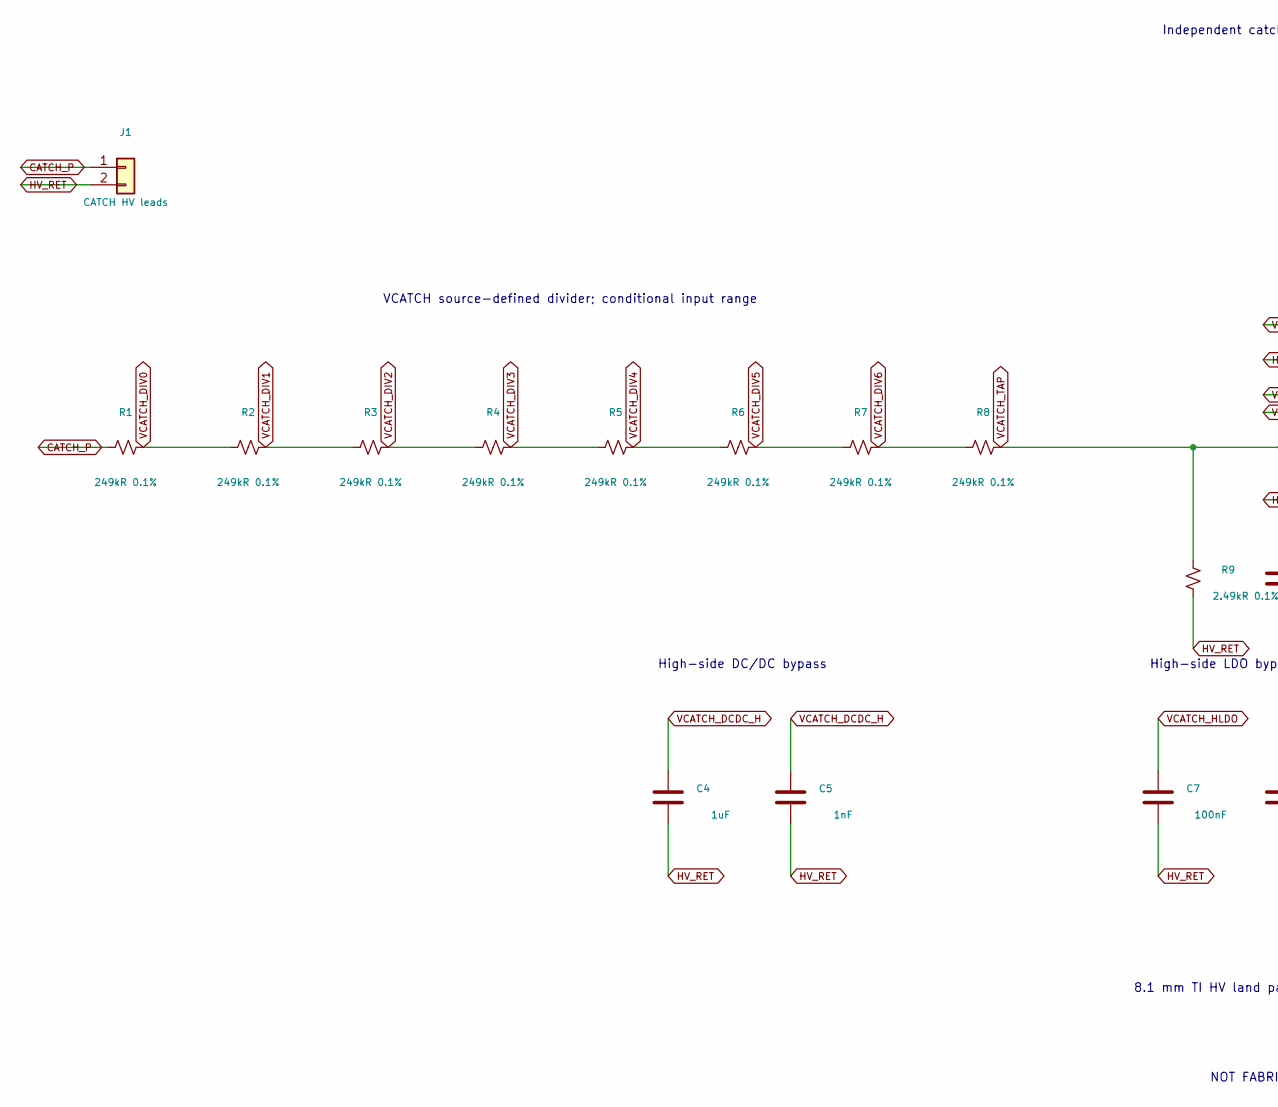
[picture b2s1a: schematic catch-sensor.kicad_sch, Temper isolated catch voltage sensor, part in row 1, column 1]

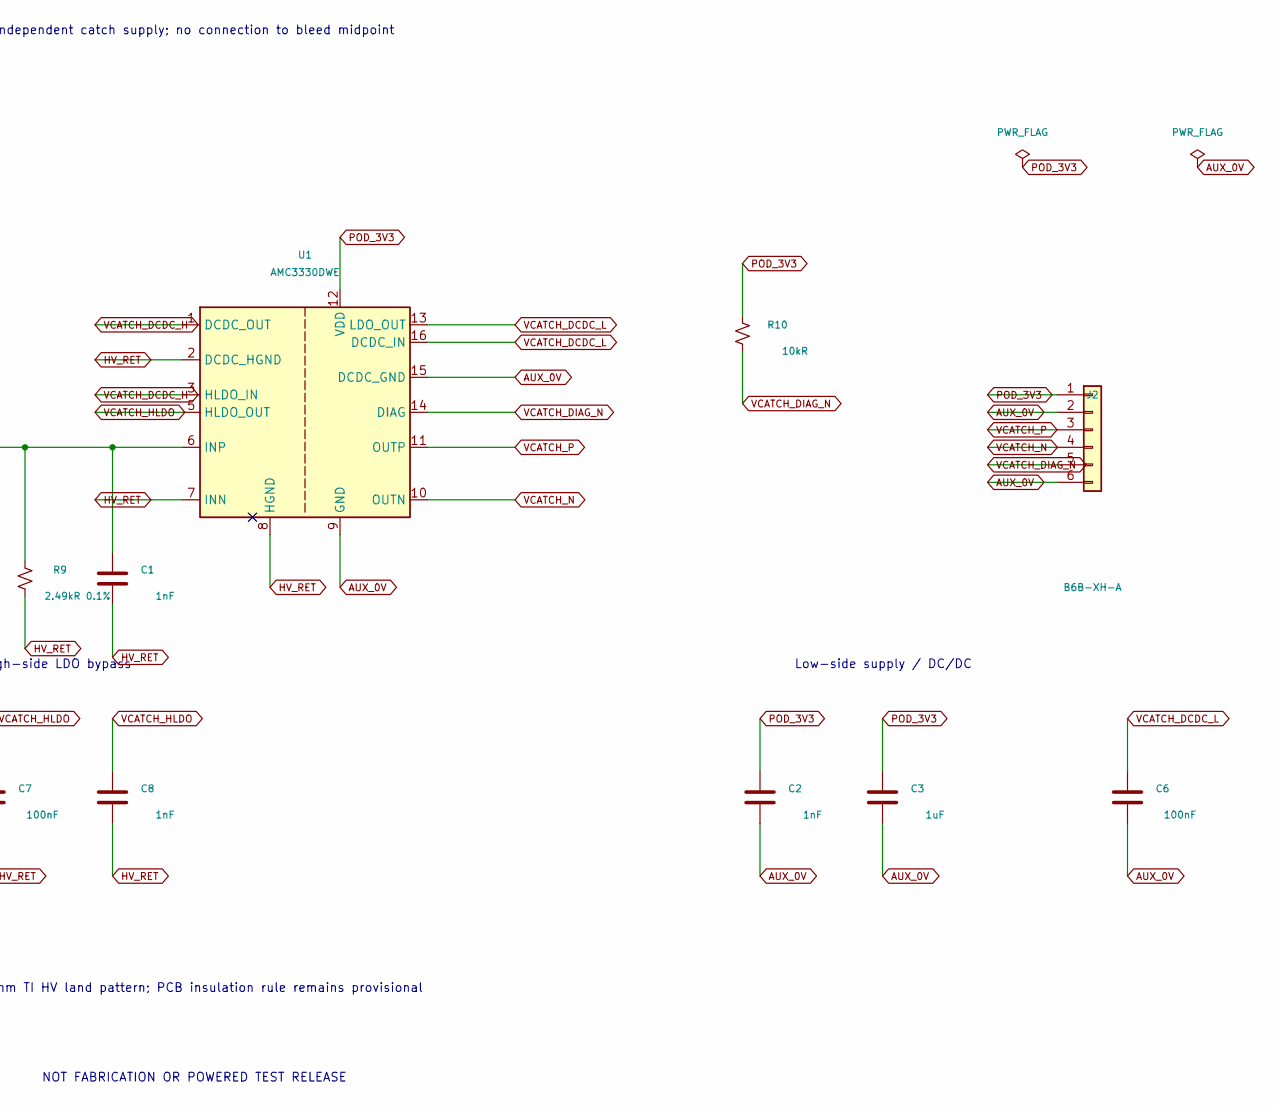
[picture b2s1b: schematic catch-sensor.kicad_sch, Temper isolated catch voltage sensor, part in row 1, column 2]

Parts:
C1: 1nF; C_0603_1608Metric; MPN 1nF C0603C102J5GACTU
C2: 1nF; C_1206_3216Metric; MPN 1nF 12065C102KAT2A
C3: 1uF; C_1206_3216Metric; MPN 1uF 12063C105KAT2A
C4: 1uF; C_0603_1608Metric; MPN 1uF CGA3E1X7R1E105K080AC
C5, C8: 1nF; C_0603_1608Metric; MPN 1nF C0603C102K5RACTU
C6, C7: 100nF; C_0603_1608Metric; MPN 100nF C0603C104K5RACAUTO
J1: CATCH HV leads; HV_WirePair_P25; MPN 22AWG_1000V_SOLDER_LEADS_WITH_EXTERNAL_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
J2: B6B-XH-A; JST_XH_B6B-XH-A_1x06_P2.50mm_Vertical; MPN B6B-XH-A(LF)(SN)
R1, R2, R3, R4, R5, R6, R7, R8: 249kR 0.1%; R_1206_3216Metric; MPN TNPW1206249KBEEA 249kR 0.1%
R9: 2.49kR 0.1%; R_1206_3216Metric; MPN TNPW12062K49BEEA 2.49kR 0.1%
R10: 10kR; R_0603_1608Metric; MPN 10kR CRCW060310K0FKEA
U1: AMC3330DWE; AMC3330_DWE_HV; MPN AMC3330DWE

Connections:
AUX_0V: C2.2, C3.2, C6.2, J2.2, J2.6, U1.9 (GND), U1.15 (DCDC_GND)
CATCH_P: J1.1, R1.1
HV_RET: C1.2, C4.2, C5.2, C7.2, C8.2, J1.2, R9.2, U1.2 (DCDC_HGND), U1.7 (INN), U1.8 (HGND)
POD_3V3: C2.1, C3.1, J2.1, R10.1, U1.12 (VDD)
VCATCH_DCDC_H: C4.1, C5.1, U1.1 (DCDC_OUT), U1.3 (HLDO_IN)
VCATCH_DCDC_L: C6.1, U1.13 (LDO_OUT), U1.16 (DCDC_IN)
VCATCH_DIAG_N: J2.5, R10.2, U1.14 (DIAG)
VCATCH_DIV0: R1.2, R2.1
VCATCH_DIV1: R2.2, R3.1
VCATCH_DIV2: R3.2, R4.1
VCATCH_DIV3: R4.2, R5.1
VCATCH_DIV4: R5.2, R6.1
VCATCH_DIV5: R6.2, R7.1
VCATCH_DIV6: R7.2, R8.1
VCATCH_HLDO: C7.1, C8.1, U1.5 (HLDO_OUT)
VCATCH_N: J2.4, U1.10 (OUTN)
VCATCH_P: J2.3, U1.11 (OUTP)
VCATCH_TAP: C1.1, R8.2, R9.1, U1.6 (INP)

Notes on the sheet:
VCATCH source-defined divider; conditional input range
Independent catch supply; no connection to bleed midpoint
8.1 mm TI HV land pattern; PCB insulation rule remains provisional
High-side DC/DC bypass
High-side LDO bypass
Low-side supply / DC/DC
NOT FABRICATION OR POWERED TEST RELEASE

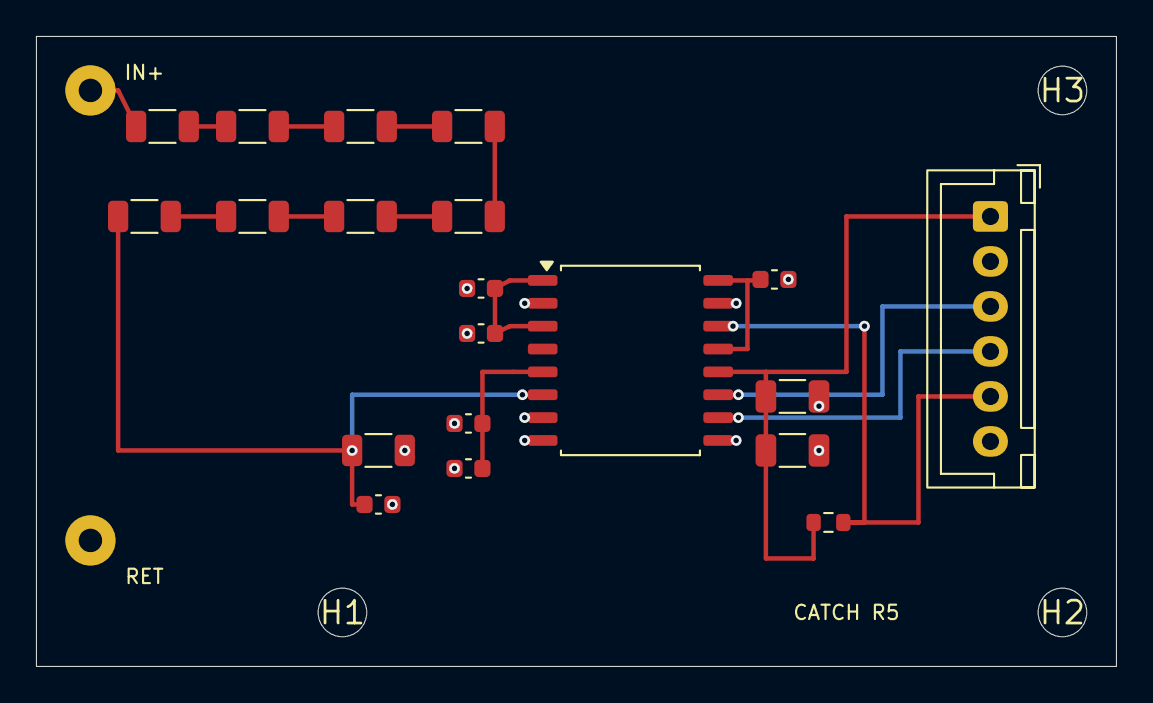
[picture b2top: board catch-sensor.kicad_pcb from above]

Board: 2 copper layers, 60.0 x 35.0 mm, 24 parts (0 on the bottom side), 18 nets.

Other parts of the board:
H1, H2, H3: (no value)

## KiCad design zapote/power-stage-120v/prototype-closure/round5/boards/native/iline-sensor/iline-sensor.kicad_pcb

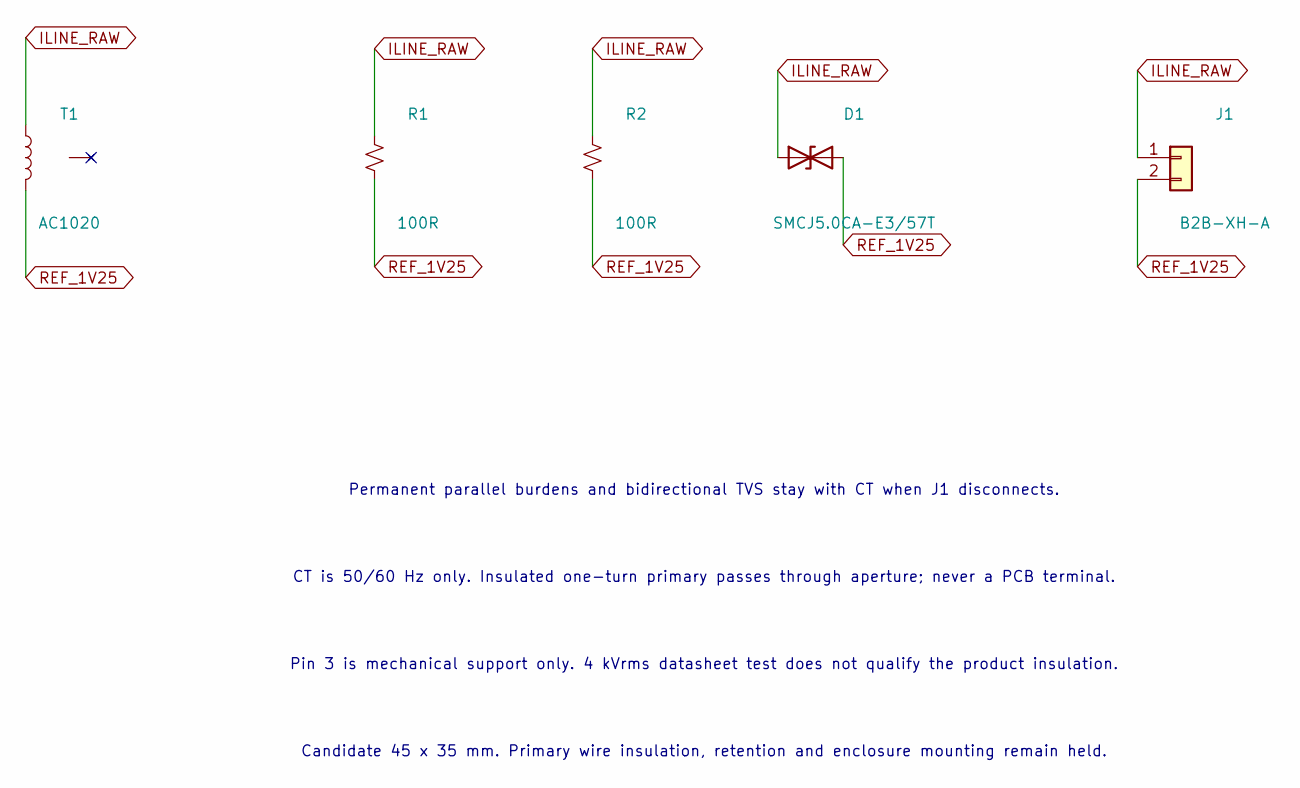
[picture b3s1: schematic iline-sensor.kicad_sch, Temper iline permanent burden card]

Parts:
D1: SMCJ5.0CA-E3/57T; D_SMC; MPN SMCJ5.0CA-E3/57T
J1: B2B-XH-A; JST_XH_B2B-XH-A_1x02_P2.50mm_Vertical; MPN B2B-XH-A(LF)(SN)
R1, R2: 100R; R_1206_3216Metric; MPN 100R CRCW1206100RFKEA
T1: AC1020; Talema_AC1005_AC1020; MPN AC1020

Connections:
ILINE_RAW: D1.1 (A1), J1.1, R1.1, R2.1, T1.1
REF_1V25: D1.2 (A2), J1.2, R1.2, R2.2, T1.2

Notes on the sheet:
Permanent parallel burdens and bidirectional TVS stay with CT when J1 disconnects.
CT is 50/60 Hz only. Insulated one-turn primary passes through aperture; never a PCB terminal.
Pin 3 is mechanical support only. 4 kVrms datasheet test does not qualify the product insulation.
Candidate 45 x 35 mm. Primary wire insulation, retention and enclosure mounting remain held.

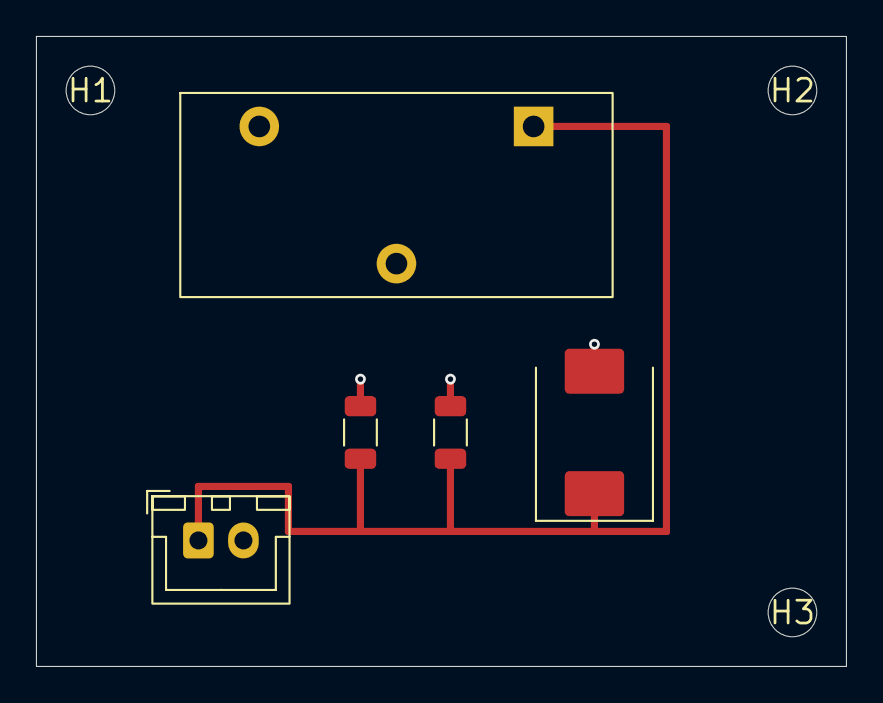
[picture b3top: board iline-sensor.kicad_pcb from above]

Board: 2 copper layers, 45.0 x 35.0 mm, 8 parts (0 on the bottom side), 2 nets.

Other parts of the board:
H1, H2, H3: (no value)
